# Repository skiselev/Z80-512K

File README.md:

# Z80-512K
Z80 CPU, 512 KiB SRAM, and 512 KiB Flash ROM module for RCBus systems

## Table of Content
* [Overview](#overview)
  * [Specifications](#specifications)
* [Assembly Instructions](#assembly-instructions)
* [Hardware Documentation](#hardware-documentation)
  * [Schematic and PCB Layout](#schematic-and-pcb-layout)
  * [Input/Output Ports](#inputoutput-ports)
  * [Connectors](#connectors)
  * [Bill of Materials](#bill-of-materials)
  * [CPLD Fuse Map](#cpld-fuse-map)
* [Release Notes](#release-notes)
  * [Changes](#changes)
  * [Known Issues](#known-issues)
* [Red Tape](#red-tape)
  * [Licensing](#licensing)
  * [Trademarks](#trademarks)

## Overview
Z80-512K is an RCBus and RC2014* compatible module, designed to run RomWBW firmware including CP/M, ZSDOS, and various applications under these OSes. Z80-512K combines functionality of the following RC2014* modules on a single module, thus saving space on the backplane:
* Z80 CPU Module
* 512k ROM 512k RAM Module
* Clock and Reset Module

In addition to these functions, Z80-512K includes programmable CLK2 clock divider, support for battery-backed SRAM, power failure NMI generation, and a watchdog.

Minimal CP/M computer system can be built using Z80-512K module, a backplane, and a serial port module, such as Z80 SIO or MC68B50 ACIA. For configurable baud rate settings, it is recommened to use serial modules that can use CLK2 as a clock, for example Steve Cousins' [SC716](https://smallcomputercentral.com/sc716-rcbus-z80-sio-2-serial-module/) or [SC725](https://smallcomputercentral.com/sc725-rcbus-serial-and-timer-module/) modules.  Additional storage module is not required, since RomWBW utilizes part of ROM and SRAM for ROM and RAM disks respecitvely, but a Compact Flash module can be added for additional storage. For a compact system, a 3-slot [SC723](https://smallcomputercentral.com/sc723-rcbus-backplane-3/) can be used.

### Specifications
* Processor: Zilog* Z80 CPU (CMOS version - Z84C00)
* Memory: 512 KiB battery-backed SRAM, 512 KiB Flash ROM, Zeta SBC V2 compatible memory pager
* Bus: RC2014* compatible
* Microprocessor Supervisor:
  * Reset generation
  * SRAM battery backup
  * Power failure NMI
  * Watchdog

## Assembly Instructions

Please refer to [Assembly Instructions](Assembly_Instructions.md) document

## Hardware Documentation

### Documentation for the Previous Versions

* [Version 1.2](https://github.com/skiselev/Z80-512K/tree/v1.2)

### Schematic and PCB Layout

* [Schematic - Version 2.0](KiCad/Z80-512K-Schematic-2.0.pdf)
* [PCB Layout - Version 2.0](KiCad/Z80-512K-Board-2.0.pdf)

### Input/Output Ports
Z80-512K uses an Atmel* ATF1504AS CPLD (complex programmable logic device) to implement Zeta SBC V2 compatible memory pager, watchdog control, and UART clock divider.
These functions are configured using registers that are accessible using I/O ports. Upon reset, the configuration registers are set to values that result in an RC2014 compatible configuration, so that RomWBW RCZ80_std.rom image can be used without any modifications.

The following I/O ports are implemented in the CPLD:

#### 0x6D - CONFIG - UART Clock Divisor and Watchdog Configuration (Read/Write)

Bits 0-4 define the ratio the 7.3728 MHz CPU clock (CLK1) is divided by to produce UART clock (CLK2).
The output clock can be calculated using the following formula: **f<sub>CLK2</sub> (Hz) = 7372800 / (3<sup>m</sup> * 2<sup>n</sup>)**, where **m** is bit 4 of **CONFIG** register (0 or 1), and **n** are bits 3-0 of **CONFIG** register (0 to 15)

Port | Bit # | Function                | Value = 0             | Value = 1
-----|-------|-------------------------|-----------------------|----------------------
0x6D | 0     | Divide CPU clock by 2   | Disable divide by 2   | Enable divide by 2
0x6D | 1     | Divide CPU clock by 4   | Disable divide by 4   | Enable divide by 4
0x6D | 2     | Divide CPU clock by 16  | Disable divide by 16  | Enable divide by 16
0x6D | 3     | Divide CPU clock by 256 | Disable divide by 256 | Enable divide by 256
0x6D | 4     | Divide CPU clock by 3   | Disable divide by 3   | Enable divide by 3

* Note: Bits 0-4 are reset to '0' on power-on or reset, so that the divide ratio is set to 1 and the CLK2 frequency is 7.3728 MHz

Bit 5 enables or disables the watchdog and controls the generation of watchdog (WDOG) signal. On the board the WDOG signal is connected to the CPU supervisor IC U5 ADM693A. The CPU supervisor will reset the board if WDOG signal is not pulsed within 1.6 seconds.
When watchdog is disabled, the /M1 signal is routed to WDOG signal, so that it is pulsed on every instruction fetch. When watchdog is enabled, the WDOG signal should be pulsed by writting to WDOG register, port 0x6F (see below) in intervals of less than 1.6 seconds.

Port | Bit # | Function                | Value = 0             | Value = 1
-----|-------|-------------------------|-----------------------|----------------------
0x6D | 5     | Watchdog enable         | Disable watchdog      | Enable watchdog

* Note: Bit 5 is reset to '0' on power-on or reset, so that watchdog is disabled

Port | Bit # | Function                                         | Value
-----|-------|--------------------------------------------------|-----------------------
0x6D | 7-6   | Not implemented                                  | Should be set to 0

#### 0x6F - WDOG - Reset Watchdog (Write-only)

Any write to this port pulses the WDOG signal, which resets the watchdog in the CPU supervisor U5

Port | Bit # | Function                | Value
-----|-------|-------------------------|---------------------------------------------
0x6F | N/A   | WDOG - Reset watchdog   | Any write to this port resets the watchdog

#### 0x78-0x7B - MPGSEL - Memory Page Select Registers (Write-only)

Port | Bit # | Function                                         | Value
-----|-------|--------------------------------------------------|-----------------------
0x78 | 5-0   | MPGSEL_0 - Page number for bank #0 0x0000-0x3FFF | 0-31 - Page number
0x78 | 7-6   | Not implemented                                  | Should be set to 0
0x79 | 5-0   | MPGSEL_1 - Page number for bank #1 0x4000-0x7FFF | 0-31 - Page number
0x79 | 7-6   | Not implemented                                  | Should be set to 0
0x7A | 5-0   | MPGSEL_2 - Page number for bank #2 0x8000-0xBFFF | 0-31 - Page number
0x7A | 7-6   | Not implemented                                  | Should be set to 0
0x7B | 5-0   | MPGSEL_2 - Page number for bank #3 0xC000-0xFFFF | 0-31 - Page number
0x7B | 7-6   | Not implemented                                  | Should be set to 0

#### 0x7Ch - MPGENA - Enable Memory Paging (Write-only)

Port | Bit # | Function                | Value = 0             | Value = 1
-----|-------|-------------------------|-----------------------|----------------------
0x7C | 0     | Memory paging enable    | Disable memory paging | Enable memory paging

* Note: The register is reset to '0' on power-on or reset, which disables the memory paging. When memory paging is disabled the memory page 0 (lower 16 KiB of the Flash ROM) is mapped to all banks.

Port | Bit # | Function                                         | Value
-----|-------|--------------------------------------------------|-----------------------
0x7C | 7-1   | Not implemented                                  | Should be set to 0

### Connectors

#### J1 - NVRAM Battery
Connect 3V battery for SRAM backup to this connector.

**Important: If the SRAM battery backup is not desired, short J1 with a jumper. Do not leave this connector open.**

Pin | Signal Name | Description
--- | ----------- | -----------
1   | VBAT        | Positive terminal - +3V
2   | GND         | Negative terminal - ground

#### J2 - JTAG - CPLD
This connector can be used to program the U4 CPLD

Pin  | Signal Name | Description      | Pin  | Signal Name | Description
---- | ----------- | ---------------- | ---- | ----------- | ----------------
1    | TCK         | Test Clock       | 2    | GND         | Ground
3    | TDO         | Test Data Output | 4    | 5V          | 5V Power Supply - Output to JTAG adapter
5    | TMS         | Test Mode Select | 6    | NC          | No Connect
7    | NC          | No Connect       | 8    | NC          | No Connect
9    | TDI         | Test Data Input  | 10   | GND         | Ground

#### J3, J4 - RC2014* Bus
Pin   | Signal Name | Description                             | Pin   | Signal Name | Description
----- | ----------- | --------------------------------------- | ----- | ----------- | -----------
J3-1  | A15         | Address A15; Output                     | J3-41 | p41         | Reserved; Not connected
J3-2  | A14         | Address A14; Output                     | J3-42 | /BAI        | Bus Acknowledge In; Not connected
J3-3  | A13         | Address A13; Output                     | J3-43 | /BAO        | Bus Acknowledge Out; Not connected
J3-4  | A12         | Address A12; Output                     | J3-44 | p44         | Reserved; Not connected
J3-5  | A11         | Address A11; Output                     | J3-45 | p45         | Reserved; Not connected
J3-6  | A10         | Address A10; Output                     | J3-46 | p46         | Reserved; Not connected
J3-7  | A9          | Address A9; Output                      | J3-47 | p47         | Reserved; Not connected
J3-8  | A8          | Address A8; Output                      | J3-48 | p48         | Reserved; Not connected
J3-9  | A7          | Address A7; Output                      | J3-49 | A23         | Address A23; Input; Not connected
J3-10 | A6          | Address A6; Output                      | J3-50 | A22         | Address A22; Input; Not connected
J3-11 | A5          | Address A5; Output                      | J3-51 | A21         | Address A21; Input; Not connected
J3-12 | A4          | Address A4; Output                      | J3-52 | A20         | Address A20; Input; Not connected
J3-13 | A3          | Address A3; Output                      | J3-53 | A19         | Address A19; Input; Not connected
J3-14 | A2          | Address A2; Output                      | J3-54 | A18         | Address A18; Input; Not connected
J3-15 | A1          | Address A1; Output                      | J3-55 | A17         | Address A17; Input; Not connected
J3-16 | A0          | Address A0; Output                      | J3-56 | A16         | Address A16; Input; Not connected
J3-17 | GND         | Ground                                  | J3-57 | GND         | Ground
J3-18 | VCC         | Power Supply - +5V                      | J3-58 | VCC         | Power Supply - +5V
J3-19 | /M1         | Machine Cycle One; Output               | J3-59 | /RFSH       | DRAM refresh; Output
J3-20 | /RESET      | Reset; Output                           | J3-60 | PAGE         | Page ROM/RAM input; Not connected
J3-21 | CLK1        | CPU Clock; Output                       | J3-61 | CLK2        | UART Clock (programmable); Output
J3-22 | /INT        | Interrupt; Input                        | J3-62 | /BUSACK     | DMA Bus Acknowledge; Output
J3-23 | /MREQ       | Memory Request; Output                  | J3-63 | /HALT       | Halt; Output
J3-24 | /WR         | Write Request; Output                   | J3-64 | /BUSREQ     | DMA Bus Request; Input
J3-25 | /RD         | Read Request; Output                    | J3-65 | /WAIT       | Wait; Input
J3-26 | /IORQ       | Input/Output Request; Output            | J3-66 | /NMI        | Non-maskable Interrupt; Input
J3-27 | D0          | Data D0; Input/Output                   | J3-67 | D8          | Data D8; Input/Output; Not connected
J3-28 | D1          | Data D1; Input/Output                   | J3-68 | D9          | Data D9; Input/Output; Not connected
J3-29 | D2          | Data D2; Input/Output                   | J3-69 | D10         | Data D10; Input/Output; Not connected
J3-30 | D3          | Data D3; Input/Output                   | J3-70 | D11         | Data D11; Input/Output; Not connected
J3-31 | D4          | Data D4; Input/Output                   | J3-71 | D12         | Data D12; Input/Output; Not connected
J3-32 | D5          | Data D5; Input/Output                   | J3-72 | D13         | Data D13; Input/Output; Not connected
J3-33 | D6          | Data D6; Input/Output                   | J3-73 | D14         | Data D14; Input/Output; Not connected
J3-34 | D7          | Data D7; Input/Output                   | J3-74 | D15         | Data D15; Input/Output; Not connected
J3-35 | TX          | Channel 1, Transmit Data; Not Connected | J3-75 | TX2         | Channel 2, Transmit Data; Not Connected
J3-36 | RX          | Channel 1, Receive Data; Not Connected  | J3-76 | RX2         | Channel 2, Receive Data; Not Connected
J3-37 | /IRQ1       | Interrupt Request 1; Not connected      | J3-77 | /IRQ2       | Interrupt Request 2; Not connected
J3-38 | IEI         | Interrupt Enable In; Not connected      | J3-78 | p78         | Reserved; Not connected
J3-39 | IEO         | Interrupt Enable Out; Not connected     | J3-79 | p79         | Reserved; Not connected
J3-40 | USER4       | User Pin 4; Not connected               | J3-80 | USER8       | User Pin 8; Not connected

### Bill of Materials

#### Version 2.0

Mouser projects - all components except of the PCB:
* [Z80-512K V2 project](https://www.mouser.com/ProjectManager/ProjectDetail.aspx?AccessID=a4dc766274) - All components except of the PCB, CPU supervisor (optional), and JTAG header (optional).
* [Z80-512K V2 - CPU Supervisor project](https://www.mouser.com/ProjectManager/ProjectDetail.aspx?AccessID=bce8da5b24) - Components for CPU supervisor (optional).
* [Z80-512K V2 - JTAG Header project](https://www.mouser.com/ProjectManager/ProjectDetail.aspx?AccessID=c965bd23ef) - Components for JTAG header (optional).

Z80-512K project on Tindie:
* [Complete kit](https://www.tindie.com/products/weird/z80-512k-rcbus-module-kit/).
* [Z80-512K PCB, a preprogrammed CPLD and optionally a Flash ROM](https://www.tindie.com/products/weird/z80-512k-rcbus-module-pcb-and-cpld/).

Component type     | Reference | Description                                 | Quantity | Possible sources and notes 
------------------ | --------- | ------------------------------------------- | -------- | --------------------------
PCB                |           | Z80-512K PCB - Version 2.0                  | 1        | Buy from my Tindie store: [Complete kit](https://www.tindie.com/products/weird/z80-512k-rc2014-compatible-module-kit/); [Z80-512K PCB, a preprogrammed CPLD and optionally a Flash ROM](https://www.tindie.com/products/weird/z80-512k-rc2014-compatible-module-pcb-and-cpld/), or order from a PCB manufacturer of your choice using provided Gerber or KiCad files
Integrated Circuit | U1        | Z84C00xxPEG - Z80 CPU, CMOS, 40 pin DIP     | 1        | Mouser [692-Z84C0010PEG](https://www.mouser.com/ProductDetail/692-Z84C0010PEG)
Integrated Circuit | U2        | SST39SF040 - 512 KiB Flash ROM, 32 pin DIP  | 1        | Mouser [804-39SF0407CPHE](https://www.mouser.com/ProductDetail/804-39SF0407CPHE)
Integrated Circuit | U3        | AS6C4008 - 512 KiB SRAM, 32 pin DIP         | 1        | Mouser [913-AS6C4008-55PCN](https://www.mouser.com/ProductDetail/913-AS6C4008-55PCN)
Integrated Circuit | U4        | ATF1504AS - CPLD, 64 macrocells, 44 pin PLCC| 1        | Mouser [556-AF1504AS10JU44](https://www.mouser.com/ProductDetail/556-AF1504AS10JU44); Possible alternative: Altera EPM7064SLC44-10
Integrated Circuit | U5        | ADM693A - Microprocessor Supervisory Circuit| 1        | Mouser [584-ADM693ANZ](https://www.mouser.com/ProductDetail/584-ADM693ANZ). Optional: CPU reset, watchdog, and power failure NMI. Possible alternatives: MAX693, LTC693, ADM691, MAX691, LTC691, ADM695, MAX695, LTC965, LTC1235
Oscillator         | X1        | 7.3728 MHz, CMOS oscillator, half can       | 1        | Mouser [774-MXO45HS-3C-7.3](https://www.mouser.com/ProductDetail/774-MXO45HS-3C-7.3) or [520-2200B-073](https://www.mouser.com/ProductDetail/520-2200B-073/)
LED                | D1        | LED indicator, 3 mm, blue                   | 1        | Mouser [710-151033BS03000](https://www.mouser.com/ProductDetail/710-151033BS03000)
Connector          | J1        | 2 pin header with friction lock, right angle| 1        | Mouser [571-6404572](https://www.mouser.com/ProductDetail/571-6404572). Optional: battery-backed SRAM
Pin Header         | J2        | 2x5 pin header, 2.54 mm pitch, vertical     | 1        | Mouser [649-77313-118-10LF](https://www.mouser.com/ProductDetail/649-77313-118-10LF). Optional: JTAG header
Pin Header         | J3        | 2x40 pin header, 2.54 mm pitch, right angle | 1        | Mouser [517-5121TG](https://www.mouser.com/ProductDetail/517-5121TG)
Capacitor          | C1        | 10 uF, 25V, MLCC, 5 mm pitch                | 1 | Mouser [810-FG28X5R1E106MR06](https://www.mouser.com/ProductDetail/810-FG28X5R1E106MR06)
Capacitor          | C2 - C7   | 0.1 uF, 50V, MLCC, 5 mm pitch               | 6        | Mouser [594-K104K15X7RF53H5](https://www.mouser.com/ProductDetail/594-K104K15X7RF53H5). Note: C5 is optional, required if U5 installed
Resistor Array     | RN1       | 4.7 kohm, bussed, 9 pin SIP                 | 1        | Mouser [652-4609X-1LF-4.7K](https://www.mouser.com/ProductDetail/652-4609X-1LF-4.7K) or [652-4609X-AP1-472LF](https://www.mouser.com/ProductDetail/652-4609X-AP1-472LF)
Resistor Array     | RN2       | 4.7 kohm, bussed, 6 pin SIP                 | 1        | Mouser [652-4606X-1LF-4.7K](https://www.mouser.com/ProductDetail/652-4606X-1LF-4.7K) or [652-4606X-AP1-472LF](https://www.mouser.com/ProductDetail/652-4606X-AP1-472LF)
Resistor           | R1 - R5   | 10 kohm, 0.25 W, 1% tolerance, axial        | 5        | Mouser [603-MFR-25FRF5210K](https://www.mouser.com/ProductDetail/603-MFR-25FRF5210K). Optional: R1 - R4 - JTAG header, R5 - Power failure NMI	
Resistor           | R6        | 29.4 kohm, 0.25 W, 1% tolerance, axial      | 1        | Mouser [603-MFR-25FBF52-29K4](https://www.mouser.com/ProductDetail/603-MFR-25FBF52-29K4). Optional: Power failure NMI
Resistor           | R7        | 1 kohm, 0.25 W, axial                       | 1        | Mouser [603-MFR-25FRF521K](https://www.mouser.com/ProductDetail/603-MFR-25FRF521K)
Trimmer Resistor   | RV1       | 2 kohm, through hole                        | 1        | Mouser [652-3362W-1-202LF](https://www.mouser.com/ProductDetail/652-3362W-1-202LF). Optional: Power failure NMI
IC Socket          | U1        | 40 pin DIP                                  | 1        | Mouser [517-4840-6000-CP](https://www.mouser.com/ProductDetail/517-4840-6000-CP)
IC Socket          | U2, U3    | 32 pin DIP                                  | 2        | Mouser [517-4832-6000-CP](https://www.mouser.com/ProductDetail/517-4832-6000-CP)
IC Socket          | U4        | 44 pin PLCC, through hole                   | 1        | Mouser [517-8444-11B1-RK-TP](https://www.mouser.com/ProductDetail/517-8444-11B1-RK-TP)
IC Socket          | U5        | 16 pin DIP                                  | 1        | Mouser [517-4816-3000-CP](https://www.mouser.com/ProductDetail/517-4816-3000-CP). Optional: CPU reset, watchdog, and power failure NMI. Install two wire jumpers as indicated on the PCB if U5 is not used.
Oscillator Socket  | X1        | 4 pin DIP, Half Can                         | 1        | Mouser [535-1108800](https://www.mouser.com/ProductDetail/535-1108800)
Jumper             | J1        | Shunt, 2 pin 2.54 mm pitch                  | 1        | Mouser [806-SX1100-B](https://www.mouser.com/ProductDetail/806-SX1100-B). Optional: install if battery is not used, but U5 is installed
Connector Contacts | J1        | Connector contact                           | 2        | Mouser [571-14453361](https://www.mouser.com/ProductDetail/571-14453361). Optional: connector for battery enclosure, install for battery-backed SRAM
Connector Housing  | J1        | 2 pin housing, 2.54 mm pitch                | 1        | Mouser [571-13758202](https://www.mouser.com/ProductDetail/571-13758202). Optional: connector for battery enclosure, install for battery-backed SRAM
Battery holder     | J1        | 2xAAA battery enclosure with switch         | 1        | Mouser [12BH421/CS-GR](https://www.mouser.com/ProductDetail/12BH421-CS-GR). Optional: battery enclosure, install for battery-backed SRAM

### CPLD Fuse Map

Z80-512K uses Atmel ATF1504AS or Intel*/Altera* EPM7064STC44 CPLD (U4) CPLD for memory pager and varous other logic. [Atmel CPLD fuse map](CPLD/output_files/Z80_512K.jed), [Altera CPLD fuse map](CPLD/output_files/Z80_512K.pof), and the CPLD source code are provided in [CPLD](CPLD) directory of this repository. Use [ATMISP](https://www.microchip.com/en-us/products/fpgas-and-plds/spld-cplds/pld-design-resources) software to program Atmel CPLD. Use free [Altera Quartus II 13.0sp1 Web Edition](https://fpgasoftware.intel.com/13.0sp1/) to program Altera CPLD. Newer Quartus versions do not support Altera MAX7000 CPLDs.

## Release Notes

### Changes

* Version 2.0:
  * Update form factor from RC2014* compatible to RCBus
  * Move the battery connector to the edge of the board
  * Make U5, CPU Supervisor IC, optional. Add information on the silkscreen for the configuration without U5

* Version 1.2
  * Add CPU LED back. Use WDOG signal to control the LED

* Version 1.1
  * Add CPLD STATUS register read back capability
  * Remove LEDs
  * Improve PCB routing: use wider traces where possible, better ground fill
  * Add signal names on the bottom silk screen

* Version 1.0
  * Initial version

### Known Issues

* Version 1.1
  * No diagnostic LEDs
    * Workaround: Connect an external LED in series with 1 kohm resistor between U5 pin 11 (WDOG signal) and VCC signal.

* Version 1.0
  * No CPLD STATUS register read back
    * Workaround: Program CPLD with the version 1.1 fuse map. Cut LED_OUT trace at D2 LED (negative terminal), connect U4 pin 36 to U1 pin 21 (RD signal) with a piece of wire. If diagnostic LED is needed, connect negative terminal of the LED to U5 pin 11 (WDOG signal)

### Wishlist
* Consider using JST connector for the battery
  * Lower profile than TE latchable connector
  * Ready-made battery holders with JST connectors, such as [Adafruit 4191](https://www.adafruit.com/product/4191) can be used
* Add RCBUs logo

## Red Tape

### Licensing

Z80-512K is an open source hardware project certified by [Open Source Hardware Association](https://www.oshwa.org/), certification UID is [US001061](https://certification.oshwa.org/us001061.html). The hardware design itself, including schematic and PCB layout design files are licensed under the strongly-reciprocal variant of [CERN Open Hardware Licence version 2](license-cern_ohl_s_v2.txt). The CPLD VHDL code is licensed under [GNU General Public License v3](license-gpl-3.0.txt). Documentation, including this file, is licensed under the [Creative Commons Attribution-ShareAlike 4.0 International License](license-cc-by-sa-4.0.txt).

### Trademarks

* "RC2014" is a registered trademark of RFC2795 Ltd.
* Other names and brands may be claimed as the property of others.

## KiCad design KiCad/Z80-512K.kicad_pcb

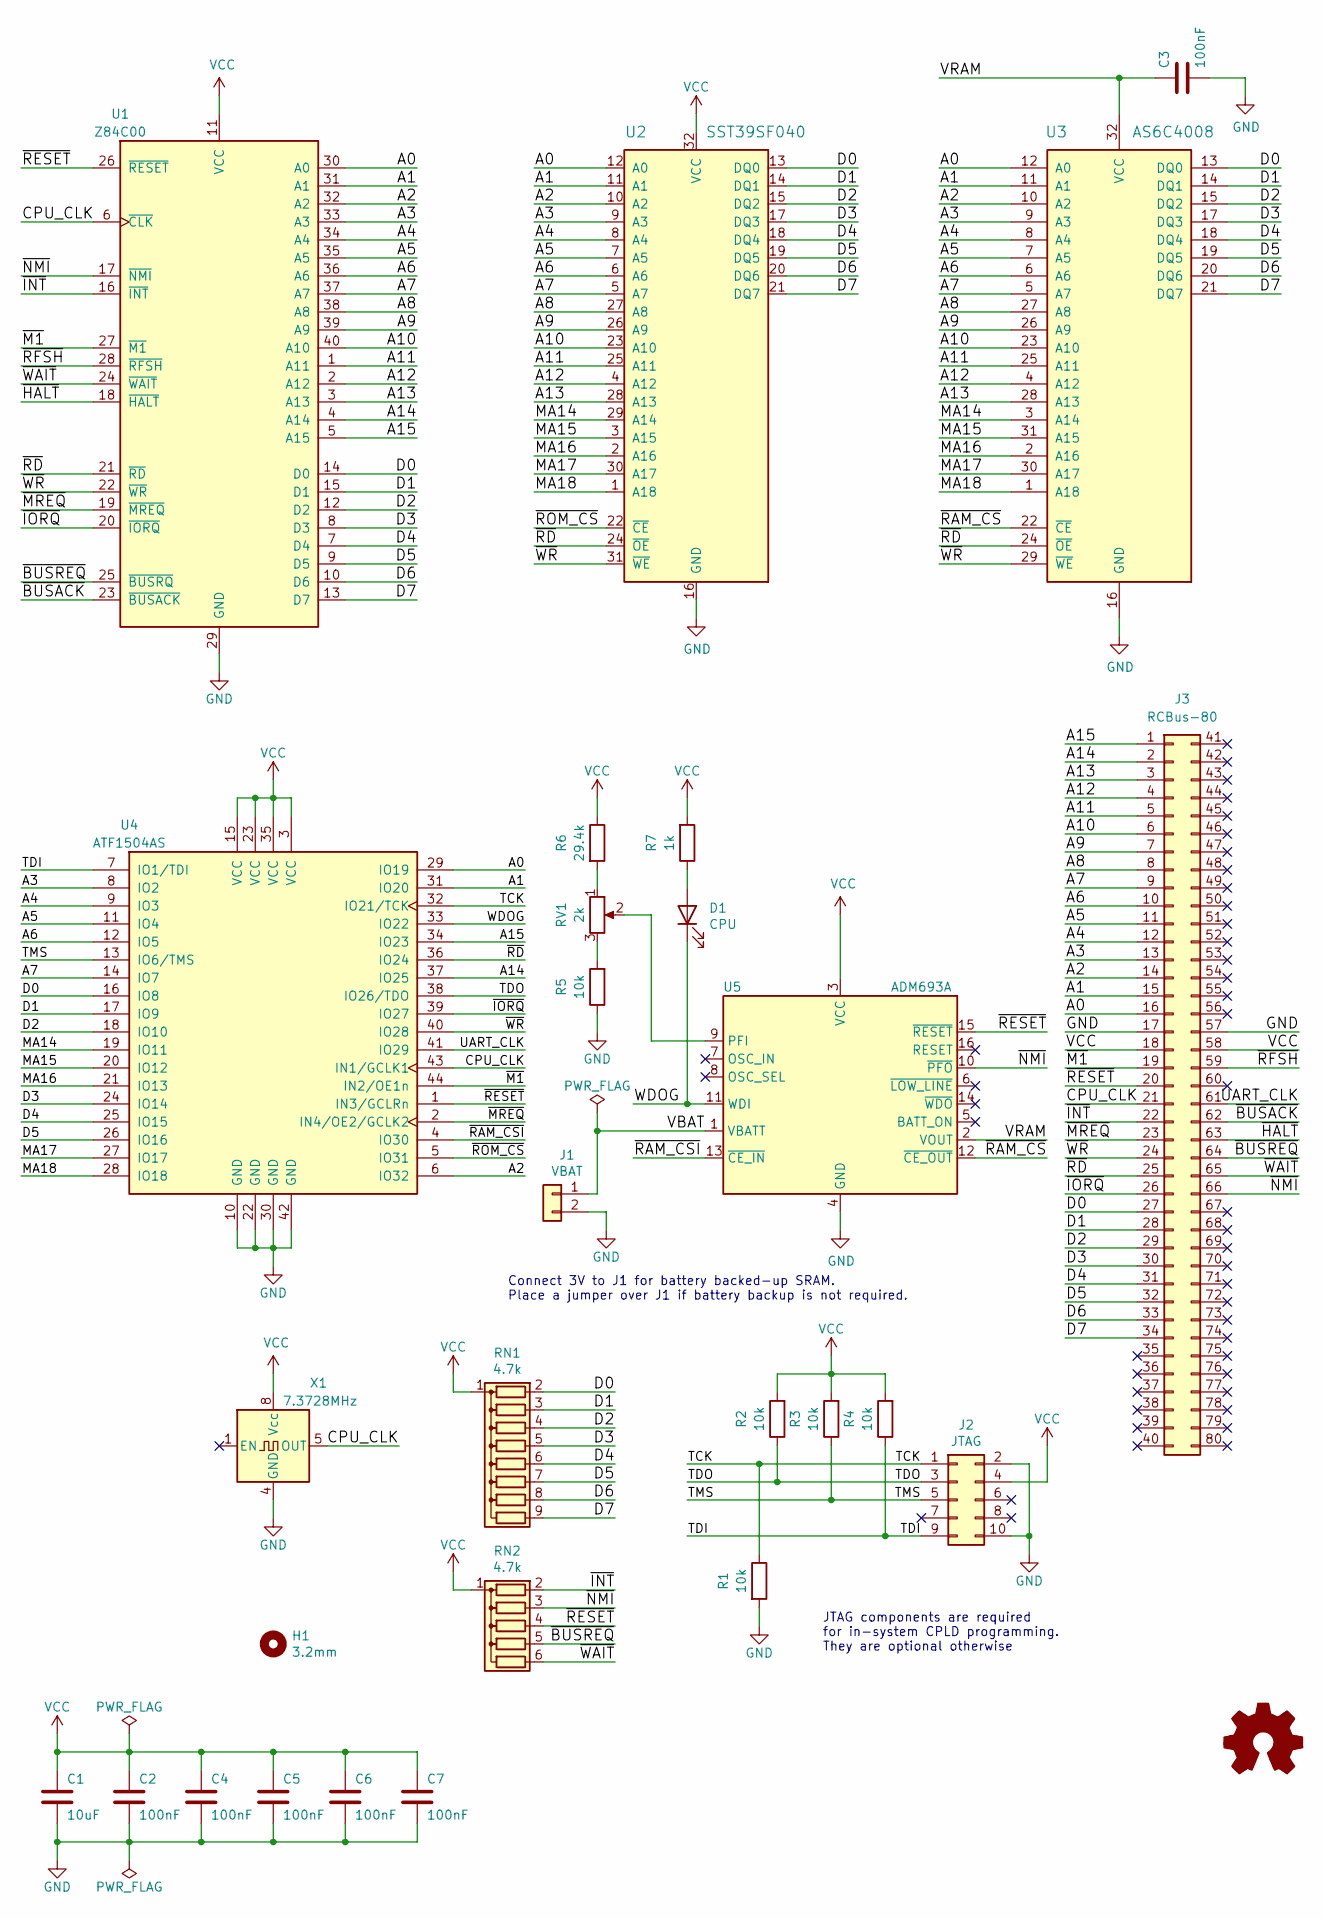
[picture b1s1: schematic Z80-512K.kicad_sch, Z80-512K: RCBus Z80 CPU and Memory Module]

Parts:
C1: 10uF; Cap_Cer_508
C2, C3, C4, C5, C6, C7: 100nF; Cap_Cer_508
D1: CPU; LED_3mm
H1: 3.2mm; MountingHole_3.2mm_M3_DIN965
J1: VBAT; PinHeader_1x02_P2.54mm_Horizontal
J2: JTAG; Conn_Pin_Header_5x2_2.54mm
J3: RCBus-80; Conn_Pin_Header_40x2_2.54mm_Right_Angle_RCBus80
LOGO1: Logo_Open_Hardware_Small; OSHW-Logo_5.7x6mm_SilkScreen
R1, R2, R3, R4, R5: 10k; R_Axial_DIN0204_L3.6mm_D1.6mm_P2.54mm_Vertical
R6: 29.4k; R_Axial_DIN0204_L3.6mm_D1.6mm_P2.54mm_Vertical
R7: 1k; R_Axial_DIN0204_L3.6mm_D1.6mm_P2.54mm_Vertical
RN1: 4.7k; Conn_SIL9
RN2: 4.7k; Conn_SIL6
RV1: 2k; Potentiometer_Bourns_3266W_Vertical
U1: Z84C00; Socket_DIP40_600
U2: SST39SF040; Socket_DIP32_600
U3: AS6C4008; Socket_DIP32_600
U4: ATF1504AS; IC_PLCC44_TH
U5: ADM693A; Socket_DIP16_300
X1: 7.3728MHz; OSC_Half_Can_DIP8

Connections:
/A0: J3.16, U1.30 (A0), U2.12 (A0), U3.12 (A0), U4.29 (IO19)
/A1: J3.15, U1.31 (A1), U2.11 (A1), U3.11 (A1), U4.31 (IO20)
/A2: J3.14, U1.32 (A2), U2.10 (A2), U3.10 (A2), U4.6 (IO32)
/A3: J3.13, U1.33 (A3), U2.9 (A3), U3.9 (A3), U4.8 (IO2)
/A4: J3.12, U1.34 (A4), U2.8 (A4), U3.8 (A4), U4.9 (IO3)
/A5: J3.11, U1.35 (A5), U2.7 (A5), U3.7 (A5), U4.11 (IO4)
/A6: J3.10, U1.36 (A6), U2.6 (A6), U3.6 (A6), U4.12 (IO5)
/A7: J3.9, U1.37 (A7), U2.5 (A7), U3.5 (A7), U4.14 (IO7)
/A8: J3.8, U1.38 (A8), U2.27 (A8), U3.27 (A8)
/A9: J3.7, U1.39 (A9), U2.26 (A9), U3.26 (A9)
/A10: J3.6, U1.40 (A10), U2.23 (A10), U3.23 (A10)
/A11: J3.5, U1.1 (A11), U2.25 (A11), U3.25 (A11)
/A12: J3.4, U1.2 (A12), U2.4 (A12), U3.4 (A12)
/A13: J3.3, U1.3 (A13), U2.28 (A13), U3.28 (A13)
/A14: J3.2, U1.4 (A14), U4.37 (IO25)
/A15: J3.1, U1.5 (A15), U4.34 (IO23)
/CPU_CLK: J3.21, U1.6 (~CLK), U4.43 (IN1/GCLK1), X1.5 (OUT)
/D0: J3.27, RN1.2 (R1), U1.14 (D0), U2.13 (DQ0), U3.13 (DQ0), U4.16 (IO8)
/D1: J3.28, RN1.3 (R2), U1.15 (D1), U2.14 (DQ1), U3.14 (DQ1), U4.17 (IO9)
/D2: J3.29, RN1.4 (R3), U1.12 (D2), U2.15 (DQ2), U3.15 (DQ2), U4.18 (IO10)
/D3: J3.30, RN1.5 (R4), U1.8 (D3), U2.17 (DQ3), U3.17 (DQ3), U4.24 (IO14)
/D4: J3.31, RN1.6 (R5), U1.7 (D4), U2.18 (DQ4), U3.18 (DQ4), U4.25 (IO15)
/D5: J3.32, RN1.7 (R6), U1.9 (D5), U2.19 (DQ5), U3.19 (DQ5), U4.26 (IO16)
/D6: J3.33, RN1.8 (R7), U1.10 (D6), U2.20 (DQ6), U3.20 (DQ6)
/D7: J3.34, RN1.9 (R8), U1.13 (D7), U2.21 (DQ7), U3.21 (DQ7)
/MA14: U2.29 (A14), U3.3 (A14), U4.19 (IO11)
/MA15: U2.3 (A15), U3.31 (A15), U4.20 (IO12)
/MA16: U2.2 (A16), U3.2 (A16), U4.21 (IO13)
/MA17: U2.30 (A17), U3.30 (A17), U4.27 (IO17)
/MA18: U2.1 (A18), U3.1 (A18), U4.28 (IO18)
/TCK: J2.1, R1.1, U4.32 (IO21/TCK)
/TDI: J2.9, R4.1, U4.7 (IO1/TDI)
/TDO: J2.3, R2.1, U4.38 (IO26/TDO)
/TMS: J2.5, R3.1, U4.13 (IO6/TMS)
/UART_CLK: J3.61, U4.41 (IO29)
/VBAT: J1.1, U5.1 (VBATT)
/VRAM: C3.2, U3.32 (VCC), U5.2 (VOUT)
/WDOG: D1.1 (K), U4.33 (IO22), U5.11 (WDI)
/~BUSACK: J3.62, U1.23 (~BUSACK)
/~BUSREQ: J3.64, RN2.5 (R4), U1.25 (~BUSRQ)
/~HALT: J3.63, U1.18 (~HALT)
/~INT: J3.22, RN2.2 (R1), U1.16 (~INT)
/~IORQ: J3.26, U1.20 (~IORQ), U4.39 (IO27)
/~M1: J3.19, U1.27 (~M1), U4.44 (IN2/OE1n)
/~MREQ: J3.23, U1.19 (~MREQ), U4.2 (IN4/OE2/GCLK2)
/~NMI: J3.66, RN2.3 (R2), U1.17 (~NMI), U5.10 (~PFO)
/~RAM_CSI: U4.4 (IO30), U5.13 (~CE_IN)
/~RAM_CS: U3.22 (~CE), U5.12 (~CE_OUT)
/~RD: J3.25, U1.21 (~RD), U2.24 (~OE), U3.24 (~OE), U4.36 (IO24)
/~RESET: J3.20, RN2.4 (R3), U1.26 (~RESET), U4.1 (IN3/GCLRn), U5.15 (~RESET)
/~RFSH: J3.59, U1.28 (~RFSH)
/~ROM_CS: U2.22 (~CE), U4.5 (IO31)
/~WAIT: J3.65, RN2.6 (R5), U1.24 (~WAIT)
/~WR: J3.24, U1.22 (~WR), U2.31 (~WE), U3.29 (~WE), U4.40 (IO28)
GND: C1.2, C2.2, C3.1, C4.2, C5.2, C6.2, C7.2, J1.2, J2.2, J2.10, J3.17, J3.57, R1.2, R5.1, U1.29 (GND), U2.16 (GND), U3.16 (GND), U4.10 (GND), U4.22 (GND), U4.30 (GND), U4.42 (GND), U5.4 (GND), X1.4 (GND)
unnamed: D1.2 (A), R7.1
unnamed: R5.2, RV1.3
unnamed: R6.2, RV1.1
unnamed: RV1.2, U5.9 (PFI)
VCC: C1.1, C2.1, C4.1, C5.1, C6.1, C7.1, J2.4, J3.18, J3.58, R2.2, R3.2, R4.2, R6.1, R7.2, RN1.1 (common), RN2.1 (common), U1.11 (VCC), U2.32 (VCC), U4.3 (VCC), U4.15 (VCC), U4.23 (VCC), U4.35 (VCC), U5.3 (VCC), X1.8 (Vcc)

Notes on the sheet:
JTAG components are required for in-system CPLD programming. They are optional otherwise
Connect 3V to J1 for battery backed-up SRAM. Place a jumper over J1 if battery backup is not required.

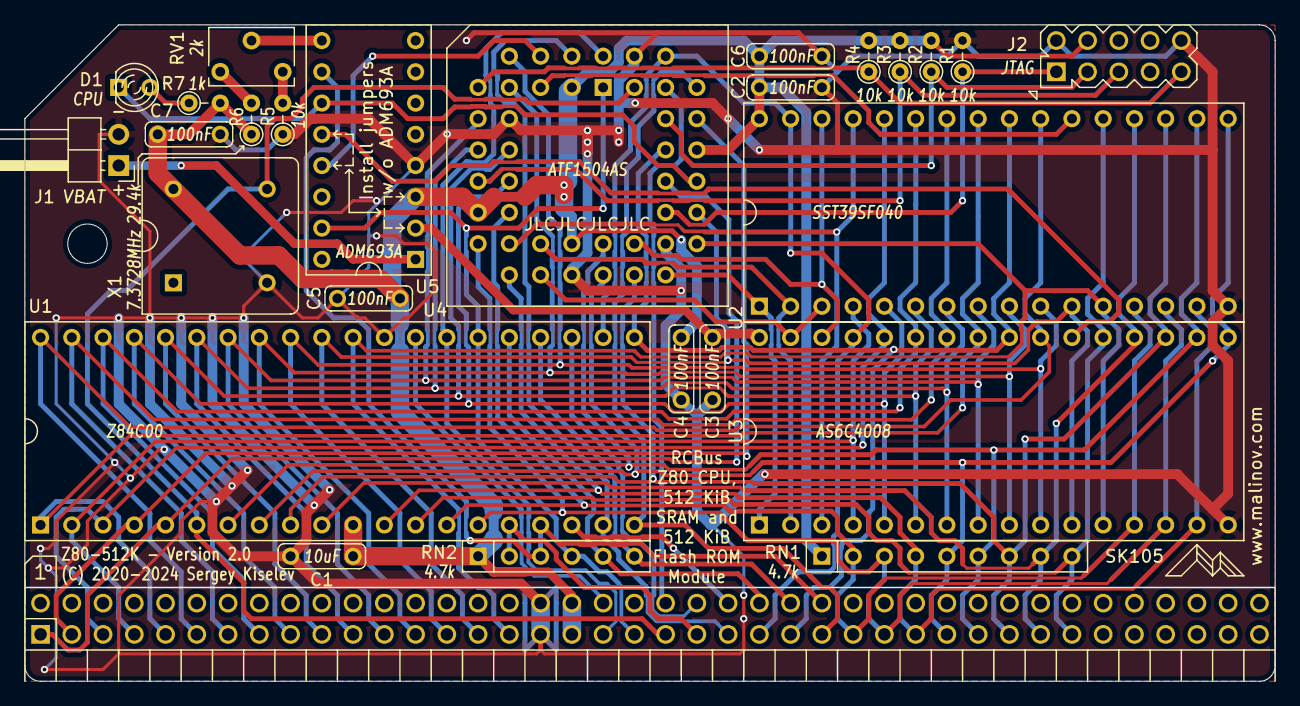
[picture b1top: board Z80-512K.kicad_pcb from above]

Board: 2 copper layers, 101.6 x 53.3 mm, 29 parts (1 on the bottom side), 60 nets.

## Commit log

2021-01-05 README: Create BOM
2021-01-05 License: Add CERN-OHL-S license
2021-01-09 Upload KiCad and Gerber files
2021-01-10 Upload CPLD files
2021-01-10 README: Add hardware information
2021-01-10 README: Update CPLD fuse map file paths
2021-01-10 Add photo of the board
2021-01-10 README: Add photo
2021-01-17 README: Add OSH Park link
2021-01-19 Add licensing information
2021-01-19 README: Typo fix
2021-01-22 README: Reformat register descriptions
2021-01-22 README: Punctuation
2021-01-22 README: Misc updates
2021-01-22 README: Misc fixes
2021-01-22 README: Use "CONFIG register" instead of port number
2021-01-22 Add GPL v3 license
2021-01-23 CPLD: Synchronous implementation for clock divider
2021-01-25 CPLD: Add LED output multiplexed with watchdog
2021-01-26 Replace design files with version 1.2. Update README accordingly
2021-01-26 README: Add table of content
2021-01-26 README: Add alternative parts for J3, J4
2021-01-27 README: Replace Introduction with an extended Overview
2021-01-27 README: typo
2021-01-28 README: Add parts for battery enclosure and connectors, add wishlist
2021-01-28 README: Add OSHWA UID
2021-01-29 README: Fix a typo (BUSREQ signal missing) in the RC2014 bus description
2021-02-05 Add photo of the board v1.2
2021-02-05 README: Update photo to v1.2
2021-02-05 Add PCB thumbnail image
2021-02-05 Add components thumbnail images
2021-02-05 Building_Instructions: Add thumbnail images
2021-02-05 Building_Instructions: Add steps to build the board
2021-02-05 Add assembly steps photos
2021-02-05 Add pictures to the assembly steps
2021-02-05 Fix images links
2021-02-05 Fix typos
2021-02-05 Add Socket DIP16 photo
2021-02-05 Add link to assembly instructions
2021-02-06 Formatting fix
2021-02-06 Try larger size component photos
2021-02-06 Try image resize
2021-02-06 Try to resize image #2
2021-02-06 Add bigger component images
2021-02-06 Add PCB rendering
2021-02-06 Assembly_Instructions: Use resized images
2021-02-07 Add higher resolution battery holder photo
2021-02-08 Assembly_Instructions: Add note about resistor arrays' orientation
2021-02-08 KiCad: Remove comment about power fail components
2021-02-12 Add alternative part numbers for the oscillator and resistor arrays
2021-02-12 Add a photo of a CP/M system
2021-02-12 Add a photo of a complete system
2021-02-12 Add Tindie links
2021-03-02 README: Update PCB sources
2022-05-03 Update Mouser links
2022-09-29 Add a note about RV1 function and adjustment
2024-01-12 Update signal names
2024-01-30 Add assembly process photos for v2.0
2024-01-30 Remove 1.2 images
2025-05-19 Update README.md
    Update the numbering of the MPGSEL_X registers

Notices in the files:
README.md:
Z80-512K is an open source hardware project certified by [Open Source Hardware Association](https://www.oshwa.org/), certification UID is [US001061](https://certification.oshwa.org/us001061.html). The hardware design itself, including schematic and PCB layout design files are licensed under the strongly-reciprocal variant of [CERN Open Hardware Licence version 2](license-cern_ohl_s_v2.txt). The CPLD VHDL code is licensed under [GNU General Public License v3](license-gpl-3.0.txt). Documentation, including this file, is licensed under the [Creative Commons Attribution-ShareAlike 4.0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
